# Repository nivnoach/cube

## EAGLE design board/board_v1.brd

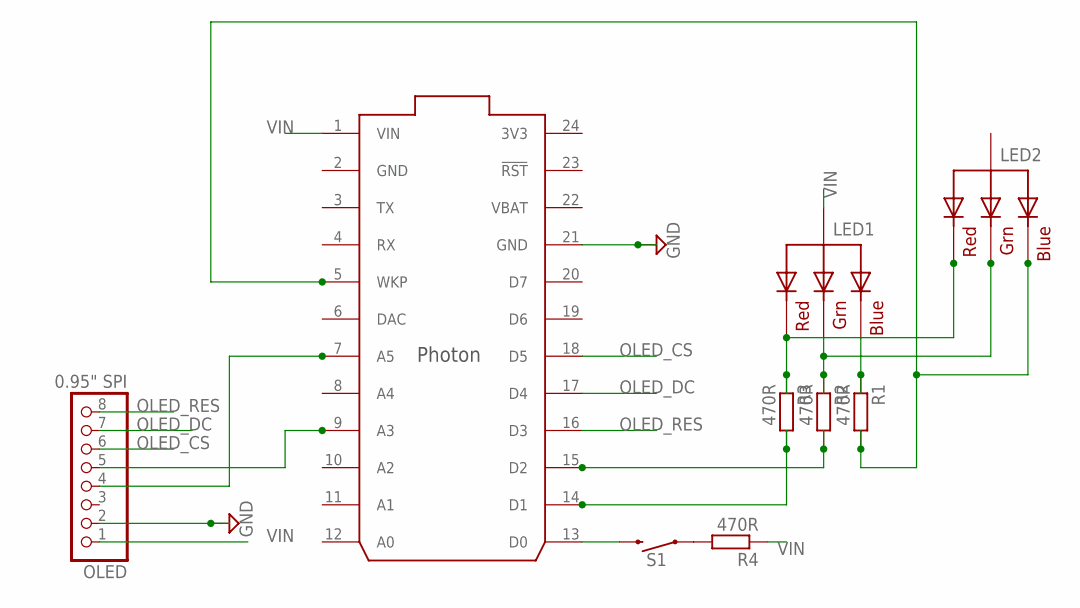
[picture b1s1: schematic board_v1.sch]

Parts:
LED1, LED2: RGBLED_CA-5MM; LED5MMRGB
OLED: 0.95" SPI; 1X08/90
R1, R2, R3, R4: 470R; 0204/7
S1: MOMENTARY-SWITCH-SPST-PTH-12MM; TACTILE_SWITCH_PTH_12MM
U$1: PHOTON_SMD

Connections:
3V3: U$1.24 (3V3)
GND: OLED.2, U$1.2 (GND), U$1.21 (GND)
unnamed: R4.2, S1.1
unnamed: S1.3 (2), U$1.13 (D0)
unnamed: LED1.4 (BLUE), R1.1
unnamed: LED1.3 (GREEN), LED2.3 (GREEN), R2.1
unnamed: LED1.1 (RED), LED2.1 (RED), R3.1
OLED_CLK: OLED.5, U$1.9 (A3)
OLED_CS: OLED.6, U$1.18 (D5)
OLED_DC: OLED.7, U$1.17 (D4)
OLED_DIN: OLED.4, U$1.7 (A5)
OLED_RES: OLED.8, U$1.16 (D3)
RGB_BLUE: LED2.4 (BLUE), R1.2, U$1.5 (WKP)
RGB_GREEN: R2.2, U$1.15 (D2)
RGB_RED: R3.2, U$1.14 (D1)
VBAT: U$1.22 (VBAT)
VIN: LED1.2 (VCC), OLED.1, R4.1, U$1.1 (VIN)

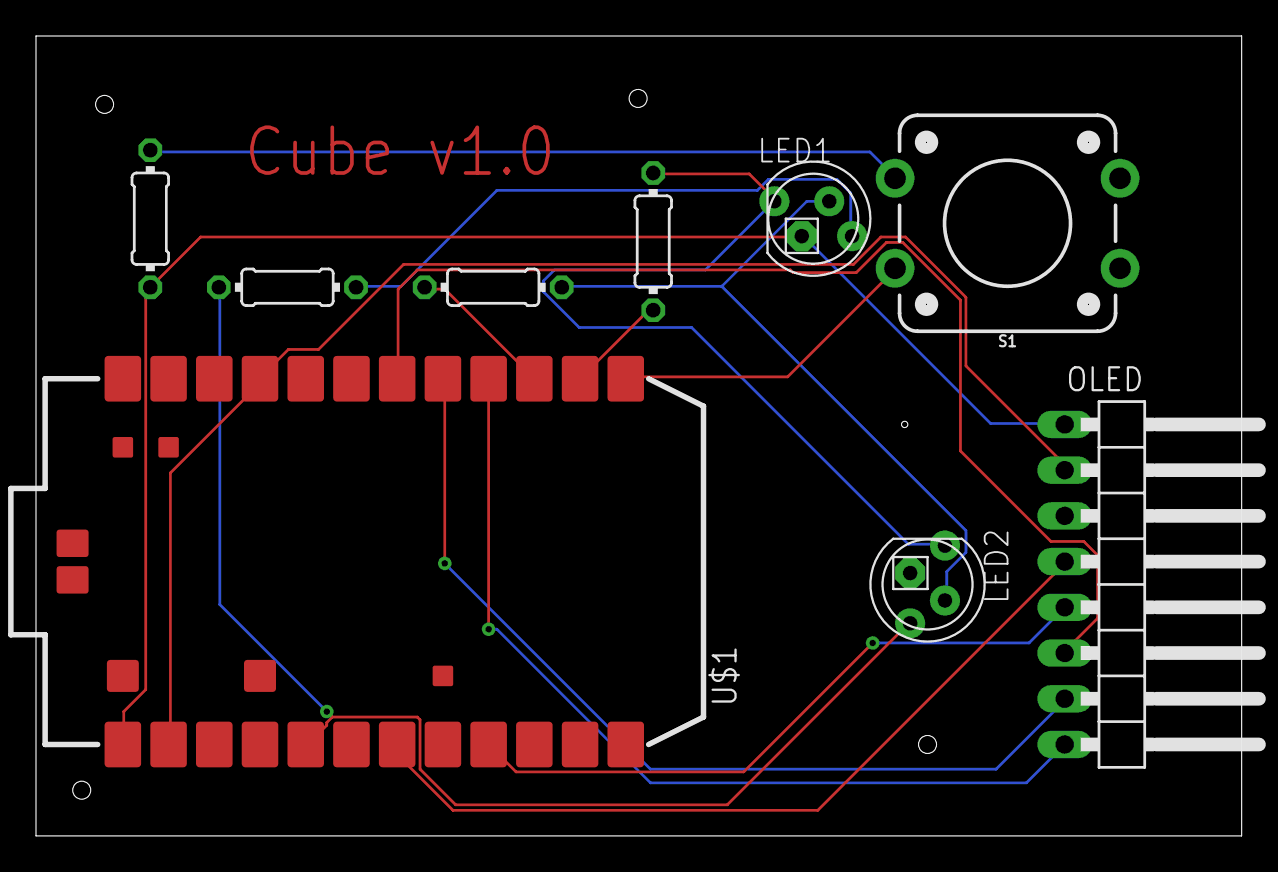
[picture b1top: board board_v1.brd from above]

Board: 2 copper layers, 67.0 x 44.4 mm, 9 parts (0 on the bottom side), 15 nets.

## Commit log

2018-02-05 First commit, bootstrap project

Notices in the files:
parts and their libraries:
SparkFun-Switches: Licensing: Creative Commons ShareAlike 4.0 International - https://creativecommons.org/licenses/by-sa/4.0
Particle-Devices: Licensing: Designed by Particle.
